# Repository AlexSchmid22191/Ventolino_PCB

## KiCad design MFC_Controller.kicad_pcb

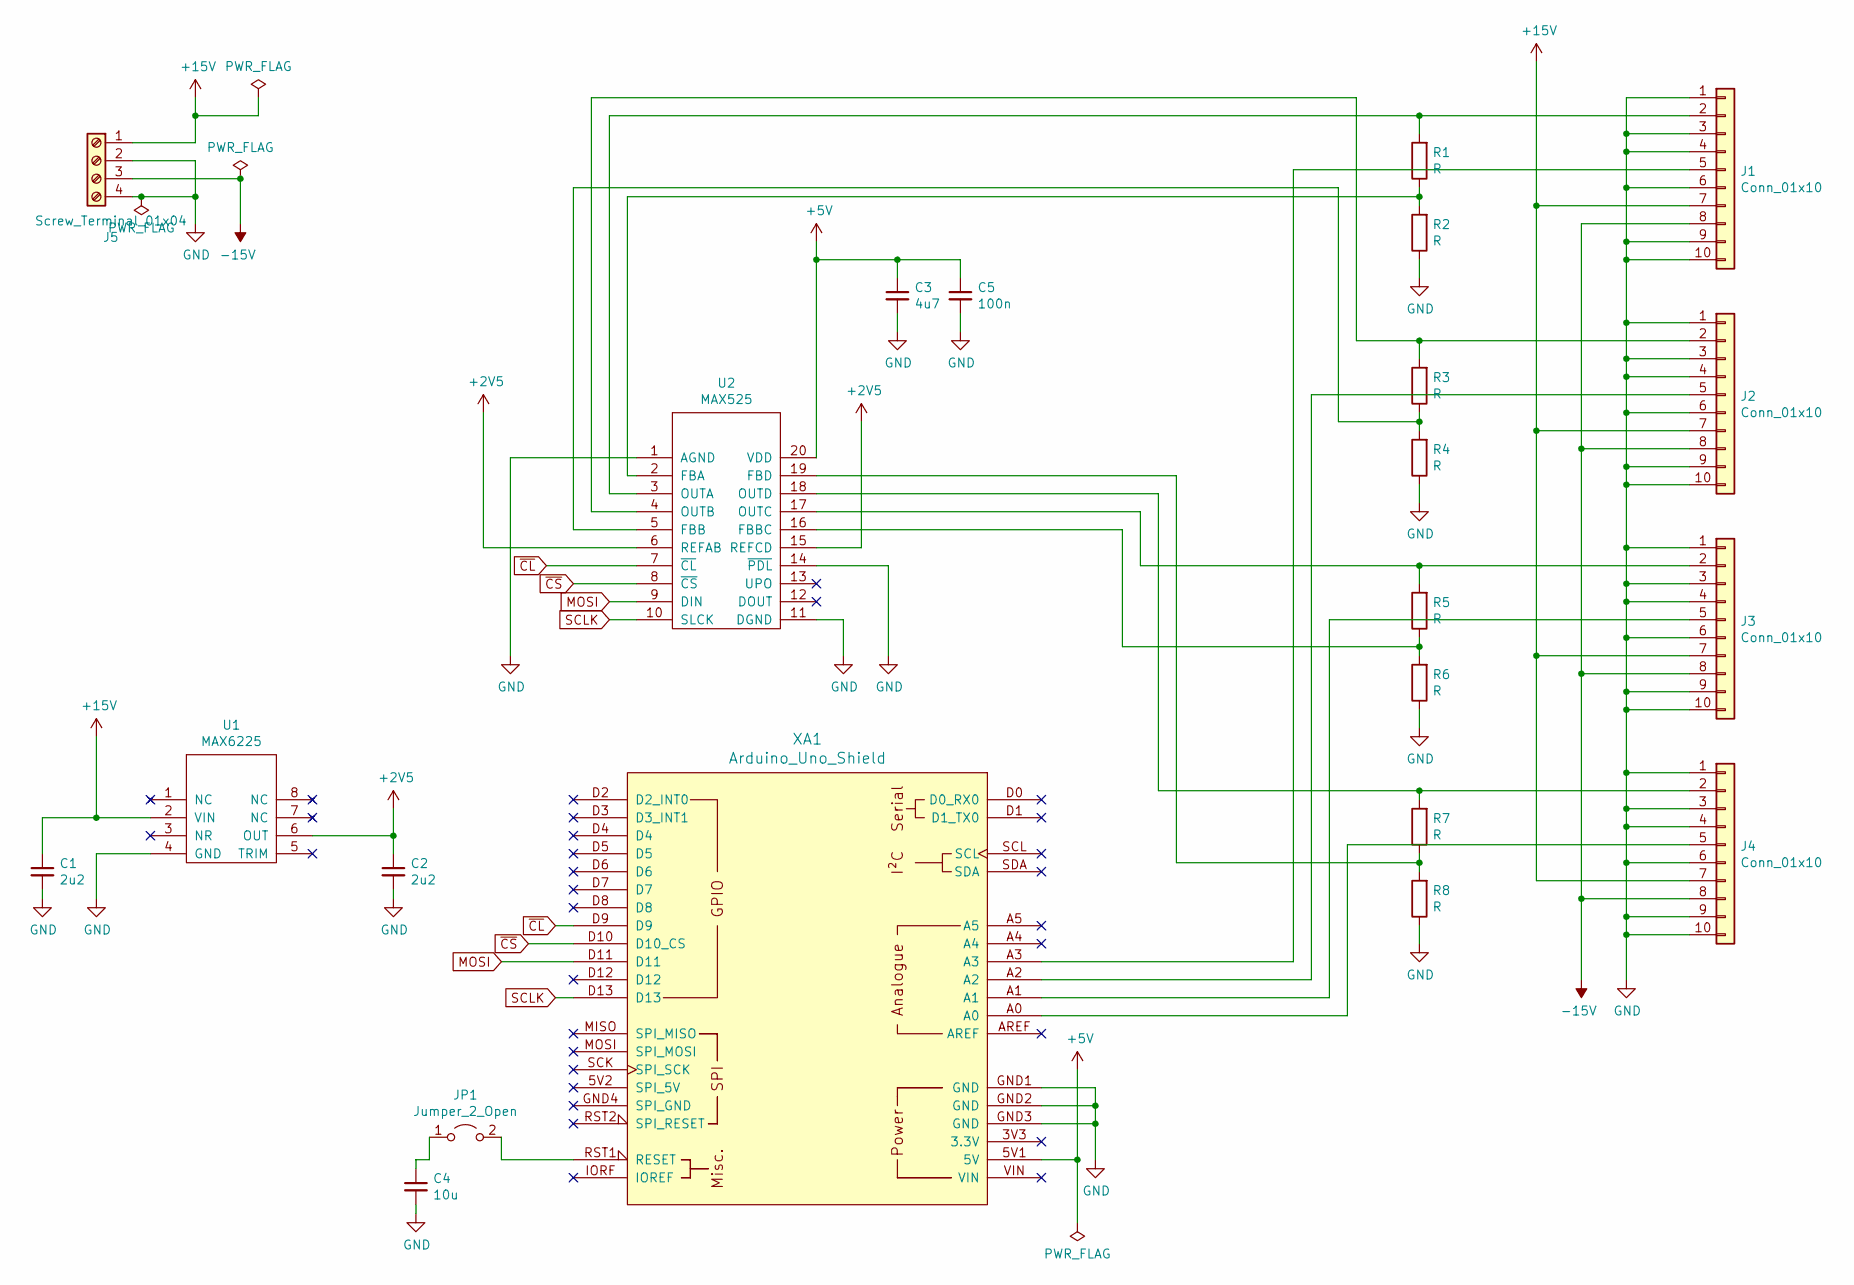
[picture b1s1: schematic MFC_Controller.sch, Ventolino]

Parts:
C1, C2: 2u2; C_0603_1608Metric_Pad1.05x0.95mm_HandSolder
C3: 4u7; C_0603_1608Metric_Pad1.05x0.95mm_HandSolder
C4: 10u; C_0603_1608Metric_Pad1.05x0.95mm_HandSolder
C5: 100n; C_0603_1608Metric_Pad1.05x0.95mm_HandSolder
J1, J2, J3, J4: Conn_01x10; IDC_05x02
J5: Screw_Terminal_01x04; RS_Srew_Term_x4
JP1: Jumper_2_Open; PinHeader_1x02_P2.54mm_Vertical
R1, R2, R3, R4, R5, R6, R7, R8: R; R_0603_1608Metric_Pad1.05x0.95mm_HandSolder
U1: MAX6225; DIP-8_W7.62mm_Socket
U2: MAX525; DIP-20_W7.62mm_Socket
XA1: Arduino_Uno_Shield

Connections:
+2V5: C2.1, U1.6 (OUT), U2.6 (REFAB), U2.15 (REFCD)
+5V: C3.1, C5.1, U2.20 (VDD), XA1.5V1 (5V)
+15V: C1.1, J1.7, J2.7, J3.7, J4.7, J5.1, U1.2 (VIN)
-15V: J1.8, J2.8, J3.8, J4.8, J5.3
GND: C1.2, C2.2, C3.2, C4.2, C5.2, J1.1, J1.3, J1.4, J1.6, J1.9, J1.10, J2.1, J2.3, J2.4, J2.6, J2.9, J2.10, J3.1, J3.3, J3.4, J3.6, J3.9, J3.10, J4.1, J4.3, J4.4, J4.6, J4.9, J4.10, J5.2, J5.4, R2.1, R4.1, R6.1, R8.1, U1.4 (GND), U2.1 (AGND), U2.11 (DGND), U2.14 (~PDL~), XA1.GND1 (GND), XA1.GND2 (GND), XA1.GND3 (GND)
MOSI: U2.9 (DIN), XA1.D11
unnamed: C4.1, JP1.1 (A), JP1.2 (B), XA1.RST1 (RESET)
unnamed: J1.2, R1.2, U2.3 (OUTA)
unnamed: J1.5, XA1.A3
unnamed: J2.2, R3.2, U2.4 (OUTB)
unnamed: J2.5, XA1.A2
unnamed: J3.2, R5.2, U2.17 (OUTC)
unnamed: J3.5, XA1.A1
unnamed: J4.2, R7.2, U2.18 (OUTD)
unnamed: J4.5, XA1.A0
unnamed: R1.1, R2.2, U2.2 (FBA)
unnamed: R3.1, R4.2, U2.5 (FBB)
unnamed: R5.1, R6.2, U2.16 (FBBC)
unnamed: R7.1, R8.2, U2.19 (FBD)
SCLK: U2.10 (SLCK), XA1.D13
~CL: U2.7 (~CL~), XA1.D9
~CS: U2.8 (~CS~), XA1.D10 (D10_CS)

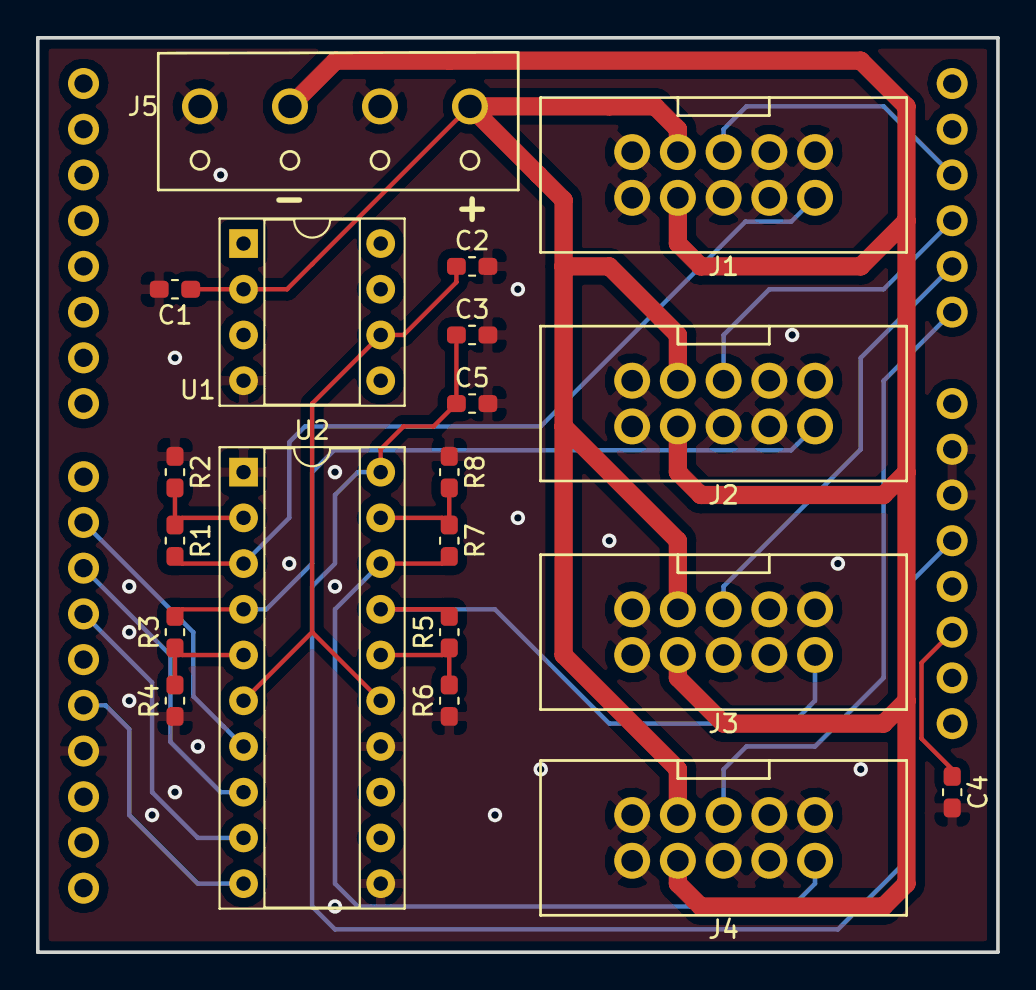
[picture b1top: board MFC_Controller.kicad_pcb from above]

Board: 2 copper layers, 53.3 x 50.8 mm, 21 parts (0 on the bottom side), 22 nets.
